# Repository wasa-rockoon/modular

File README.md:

# モジュラー電装

# バス

バスの物理規格は，2.54mmピッチのカードエッジコネクタとする．片面15ピンずつ．

CANを用いた通信プロトコルは [WCCP](https://github.com/wasa-rockoon/WCCP)を参照．

表
1. Vpp
2. Vcc 5V
3. Vdd 3.3V
4. VBAT 3V
5. GND
6. CAN Low
7. CAN High
8. GND
9. キー
10. JTMS, SWDIO
11. JTCK, SWCLK
12. JTDI
13. JTDO, TRACESWO
14. /JNTRST
15. /RESET
裏

16 ~ 23, 25 ~ 30. テスト用プローブ 1 ~ 8, 9 ~ 14

24. キー

## Vpp, Vcc, Vdd, GND

電源モジュールから供給される．バスからのVpp供給は小電流に限る．大電流が必要なモジュールには電源モジュールまたは外部から直接供給すること．

## CAN High, CAN Low

5V CANバス, Normal CAN 1Mbps

## SWCLK, SWDIO, RST

STM32書き込み・デバッグ用

# モジュール一覧

## ベース基板

6個のモジュールを搭載できるベース基板．
カードエッジコネクタのうち1つを書き込み・デバッグ用とする．

- カードエッジコネクタ x6
- CANバスコネクタ x2
- STLink 書き込み・デバッグ用コネクタ x1
- テスト用カードエッジ

### CANバスコネクタ

ベース基板に取り付けないモジュールとの中距離接続に用いる．

1. Vpp
2. CAN Low
3. CAN High
4. GND

Vcc, Vddはモジュール側で自給する．

接続しない場合は，CAN Low と CAN High との間に終端抵抗（120 Ω）を必ず接続すること．

## Battery Power

- 5Vおよび3.3Vの電源を供給
- 各系統の電圧および電流を測定

### 接続

- 電源供給（6V~18V）：XH (1: V+, 2: GND)

### インターフェース

- 主電源スイッチ
- バックアップ電源スイッチ

### 出力パケット

#### B （Battery）

| Type | Data | Description |
| --- | --- | --- |
| P | float16 | 供給電源電圧 [V] |
| C | float16 | 5V系電圧 [V] |
| D | float16 | 3.3V系電圧 [V] |
| c | float16 | 5V系電圧 [A] |
| d | float16 | 3.3V系電流 [A] |

## Battery Power V2

- 5Vおよび3.3Vの電源を供給
- 各系統の電圧および電流を測定
- 外部に5Vまたは3.3Vの電源を供給
- バッテリー温度を測定し，ヒーターを駆動

### 接続

- 電源供給1（6V~18V）：XH (1: V+, 2: GND)
- 電源供給2（6V~18V）：XH (1: V+, 2: GND)
- ヒーター：PH (1: Heater+, 2: GND, 3: temperature)
- 外部供給出力（5V or 3.3V）：PH (1: V+, 2: GND, 3: flight pin)
- 外部電源スイッチ：PH

### インターフェース

- 5V・3.3V系電源スイッチ（外部スイッチとどちらかがONならば供給）

### 出力パケット

#### B （Battery）

| Type | Data | Description |
| --- | --- | --- |
| P | float16 | 供給電源電圧 [V] |
| C | float16 | 5V系電圧 [V] |
| D | float16 | 3.3V系電圧 [V] |
| c | float16 | 5V系電圧 [A] |
| d | float16 | 3.3V系電流 [A] |

## Comm&Log

- LoRa（ES920LR）通信
- TWELITE 通信
- Micro SD カードにログを記録

### 接続

- LoRa アンテナ：U.FL
- TWELITE アンテナ：U.FL

### インターフェース

- Micro SD カードスロット

## LoRa

- LoRa（ES920LR）通信（2ch）

### 接続

- LoRa アンテナx2：U.FL

## Igniter Driver

- 発射条件を判定しイグナイタを駆動
- 供給電圧，電流，イグナイタ抵抗値を測定

### 接続

- イグナイタ用供給（6V~12V）：XH (1: V+, 2: GND)
- イグナイタ出力：XH (1: V+, 2: GND)

### インターフェース

- 警報ブザー

## Nav

- 9軸センサ（BMX055）
- 気圧センサ（BME280）
- GNSS

### 接続

- GPS パッシブアンテナ：U.FL
- UART （外部GPS用）：PH
- I2C （拡張用）：PH

## INS

- 9軸センサ（BNO055）
- 気圧センサ（BME280）
- GNSS (NEO-M9N-00B)

### 接続

- GPS アクティブアンテナ：U.FL
- サーミスタ：PH
- UART （拡張用）：PH
- I2C （拡張用）：PH

## RCS

- 電磁バルブ制御x4
- バルブ用電源（24V）供給
- 圧力計測（1MPaG）x2
- 推力計測x2
- 温度計測

### 接続

- バルブAB：PH (1: A+, 2: A-, 3: B+, 4: B-)
- バルブCD：PH (1: C+, 2: C-, 3: D+, 4: D-)
- ロードセルX：ZH (1: Vdd, 2: GND, 3: Signal+, 4: Signal-)
- ロードセルY：ZH (1: Vdd, 2: GND, 3: Signal+, 4: Signal-)
- 圧力センサ1：ZH (1: Vcc, 2: GND, 3: Signal)
- 圧力センサ2：ZH (1: Vcc, 2: GND, 3: Signal)
- サーミスタ：ZH

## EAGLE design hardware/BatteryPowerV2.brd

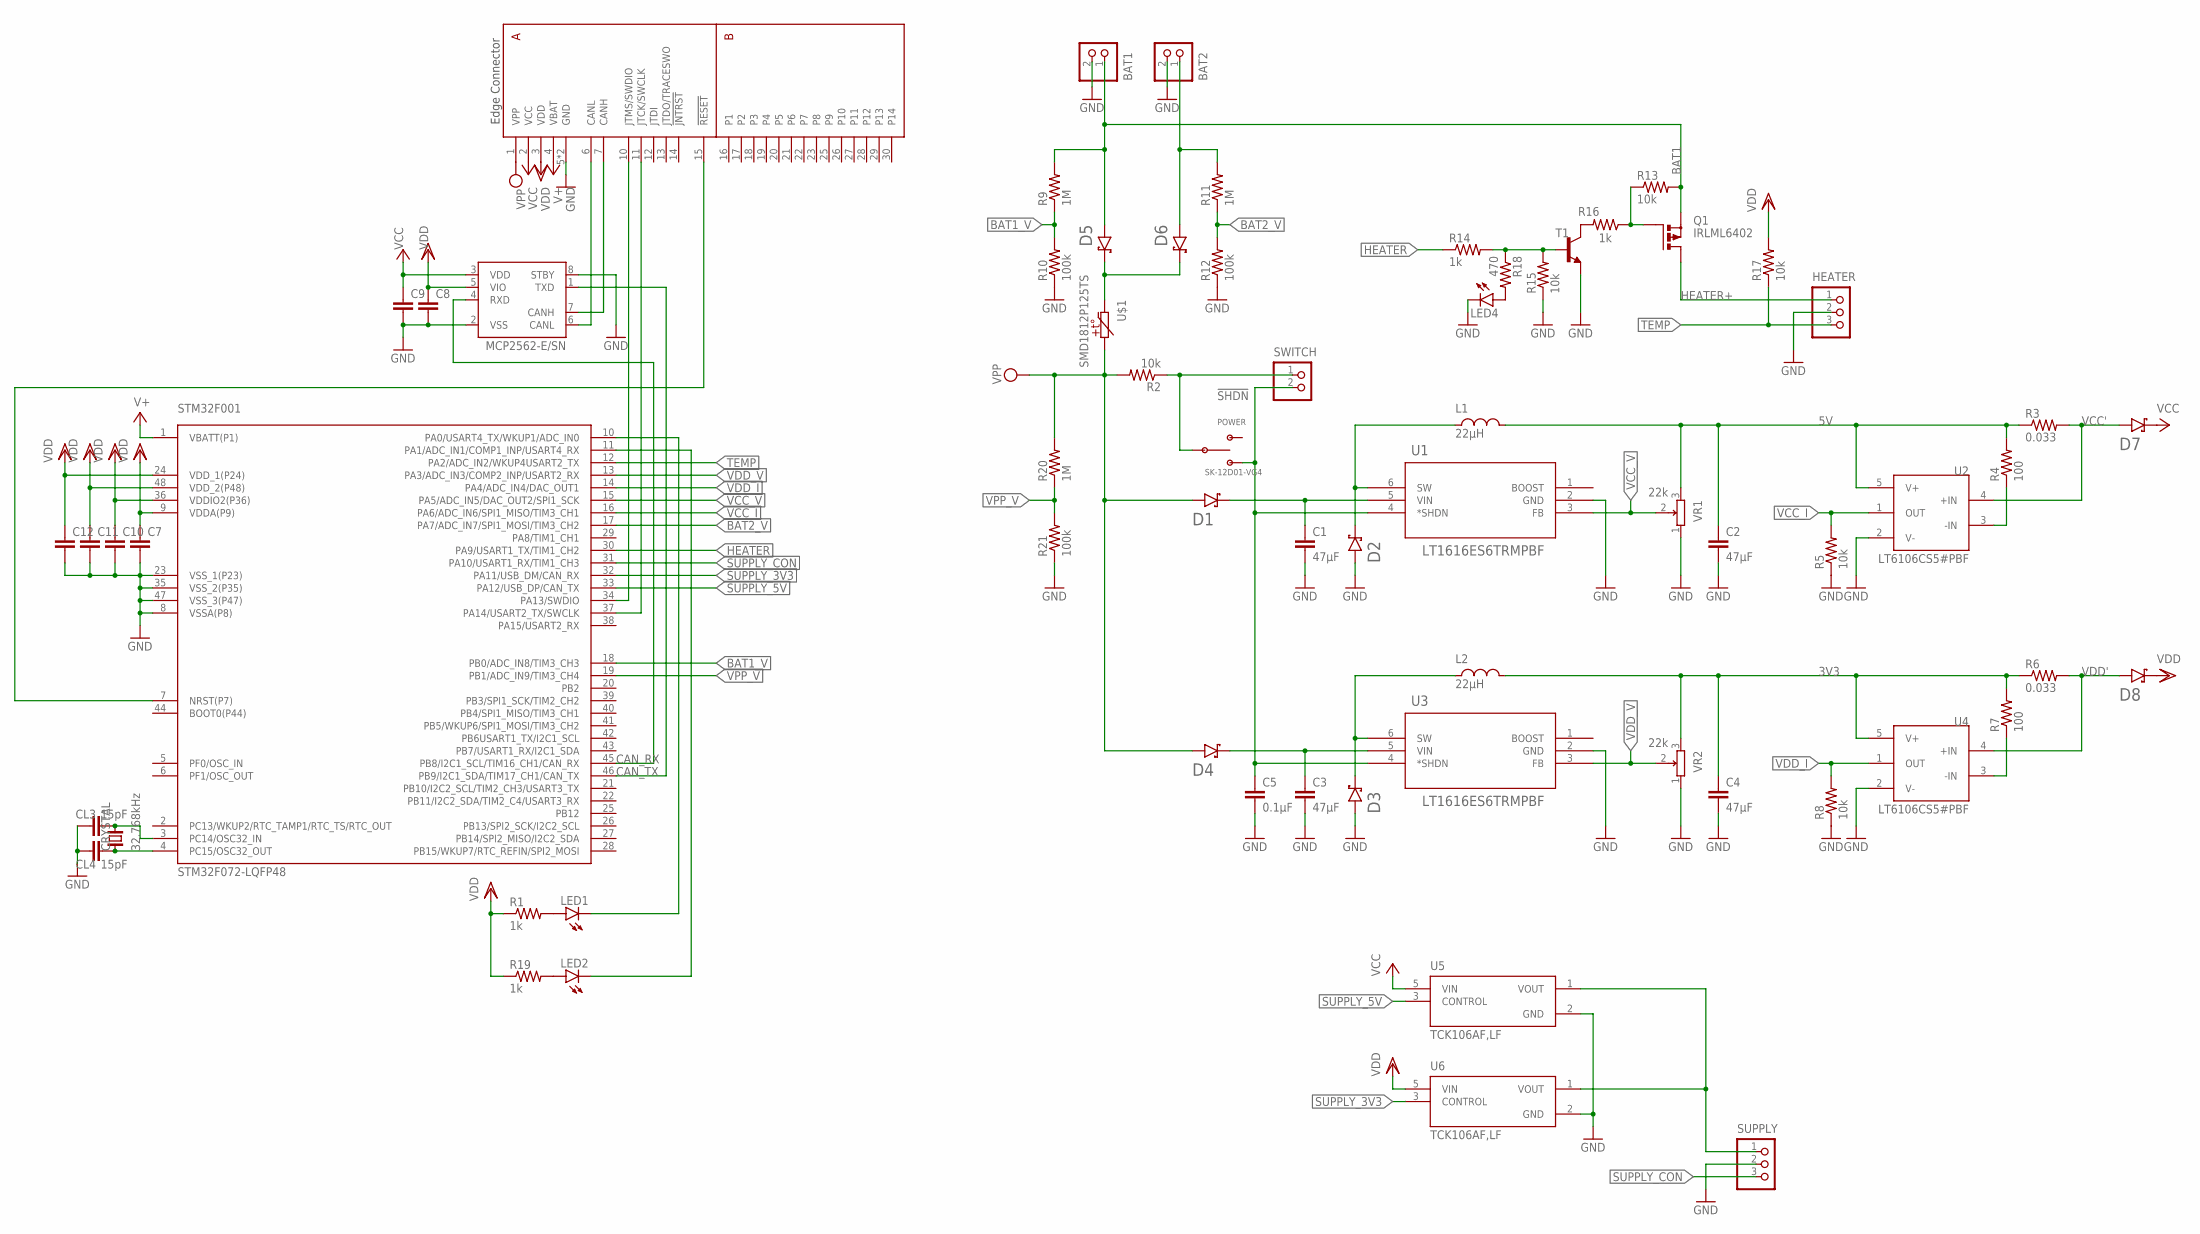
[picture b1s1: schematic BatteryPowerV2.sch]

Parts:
BAT1, BAT2: S2B-XH-A
C1, C2, C3, C4: 47µF; C0603
C5: 0.1µF; C0603
C7, C8, C9, C10, C11, C12: C-EUC0603K; C0603K
CL3, CL4: 15pF; C0603K
CRYSTAL: 32.768kHz; FC-255
D1, D2, D3, D4, D5, D6, D7, D8: CUHS20S30
HEATER: S3B-PH-K-S
L1, L2: 22µH; NR10050
LED1, LED2: LEDCHIP-LED0603; CHIP-LED0603
LED4: LEDCHIPLED_0603; CHIPLED_0603
MCP2562: MCP2562-E/SN; SOIC127P600X175-8N
POWER: SK-12D01-VG4
Q1: IRLML6402; SOT-23
R1, R14, R16, R19: 1k; R0603
R2, R5, R8, R13, R15, R17: 10k; R0603
R3, R6: 0.033; R0603
R4, R7: 100; R0603
R9, R11, R20: 1M; R0603
R10, R12, R21: 100k; R0603
R18: 470; R0603
STM32F001: STM32F072-LQFP48; LQFP48
SUPPLY: S3B-PH-K-S
SWITCH: S2B-PH-K-S
T1: -NPN-SOT23-EBC; SOT23-EBC
U1, U3: LT1616ES6TRMPBF; SOT-6_S
U2, U4: LT6106CS5#PBF; SOT95P280X100-5N_LT6106CS5#PBF
U5, U6: TCK106AF,LF; IC_TCK106AF,LF
U$1: SMD1812P125TS; SMD1812P
U$2: EDGE30
VR1, VR2: 22k; PVZ3A

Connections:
3V3: C4.1, L2.2, R6.1, R7.2, U4.5 (V+), VR2.3
5V: C2.1, L1.2, R3.1, R4.2, U2.5 (V+), VR1.3
!SHDN!: C5.1, POWER.B, SWITCH.2, U1.4 (*SHDN), U3.4 (*SHDN)
BAT1: BAT1.1, D5.A, Q1.P2 (S), R9.2, R13.2
BAT1_V: R9.1, R10.2, STM32F001.18 (PB0/ADC_IN8/TIM3_CH3)
BAT2: BAT2.1, D6.A, R11.2
BAT2_V: R11.1, R12.2, STM32F001.17 (PA7/ADC_IN7/SPI1_MOSI/TIM3_CH2)
CANH1: MCP2562.7 (CANH), U$2.7 (CANH)
CANL1: MCP2562.6 (CANL), U$2.6 (CANL)
CAN_RX: MCP2562.4 (RXD), STM32F001.45 (PB8/I2C1_SCL/TIM16_CH1/CAN_RX)
CAN_TX: MCP2562.1 (TXD), STM32F001.46 (PB9/I2C1_SDA/TIM17_CH1/CAN_TX)
GND: BAT1.2, BAT2.2, C1.2, C2.2, C3.2, C4.2, C5.2, C7.2, C8.2, C9.2, C10.2, C11.2, C12.2, CL3.1, CL4.1, D2.A, D3.A, HEATER.2, LED4.C, MCP2562.2 (VSS), MCP2562.8 (STBY), R5.1, R8.1, R10.1, R12.1, R15.1, R21.1, STM32F001.8 (VSSA(P8)), STM32F001.23 (VSS_1(P23)), STM32F001.35 (VSS_2(P35)), STM32F001.47 (VSS_3(P47)), SUPPLY.2, T1.E, U1.2 (GND), U2.2 (V-), U3.2 (GND), U4.2 (V-), U5.2 (GND), U6.2 (GND), U$2.5 (GND), U$2.8 (GND), VR1.1, VR2.1
HEATER: R14.1, STM32F001.30 (PA9/USART1_TX/TIM1_CH2)
HEATER+: HEATER.1, Q1.P3 (D)
unnamed: SUPPLY.1, U5.1 (VOUT), U6.1 (VOUT)
unnamed: R4.1, U2.3 (-IN)
unnamed: Q1.P1 (G), R13.1, R16.1
unnamed: LED2.C, STM32F001.11 (PA1/ADC_IN1/COMP1_INP/USART4_RX)
unnamed: R7.1, U4.3 (-IN)
unnamed: POWER.C, R2.1, SWITCH.1
unnamed: LED2.A, R19.2
unnamed: R14.2, R15.2, R18.1, T1.B
unnamed: R16.2, T1.C
unnamed: LED4.A, R18.2
unnamed: CL4.2, CRYSTAL.1, STM32F001.4 (PC15/OSC32_OUT)
unnamed: CL3.2, CRYSTAL.2, STM32F001.3 (PC14/OSC32_IN)
unnamed: LED1.C, STM32F001.10 (PA0/USART4_TX/WKUP1/ADC_IN0)
unnamed: LED1.A, R1.2
NRST1: STM32F001.7 (NRST(P7)), U$2.15 (!RESET!)
SUPPLY_3V3: STM32F001.32 (PA11/USB_DM/CAN_RX), U6.3 (CONTROL)
SUPPLY_5V: STM32F001.33 (PA12/USB_DP/CAN_TX), U5.3 (CONTROL)
SUPPLY_CON: STM32F001.31 (PA10/USART1_RX/TIM1_CH3), SUPPLY.3
SWCLK1: STM32F001.37 (PA14/USART2_TX/SWCLK), U$2.11 (JTCK/SWCLK)
SWDIO1: STM32F001.34 (PA13/SWDIO), U$2.10 (JTMS/SWDIO)
TEMP: HEATER.3, R17.1, STM32F001.12 (PA2/ADC_IN2/WKUP4USART2_TX)
VBAT: STM32F001.1 (VBATT(P1)), U$2.4 (VBAT)
VCC: C9.1, D7.C, MCP2562.3 (VDD), U5.5 (VIN), U$2.2 (VCC)
VCC': D7.A, R3.2, U2.4 (+IN)
VCC_I: R5.2, STM32F001.16 (PA6/ADC_IN6/SPI1_MISO/TIM3_CH1), U2.1 (OUT)
VCC_IN: C1.1, D1.C, U1.5 (VIN)
VCC_SW: D2.C, L1.1, U1.6 (SW)
VCC_V: STM32F001.15 (PA5/ADC_IN5/DAC_OUT2/SPI1_SCK), U1.3 (FB), VR1.2
VDD: C7.1, C8.1, C10.1, C11.1, C12.1, D8.C, MCP2562.5 (VIO), R1.1, R17.2, R19.1, STM32F001.9 (VDDA(P9)), STM32F001.24 (VDD_1(P24)), STM32F001.36 (VDDIO2(P36)), STM32F001.48 (VDD_2(P48)), U6.5 (VIN), U$2.3 (VDD)
VDD': D8.A, R6.2, U4.4 (+IN)
VDD_I: R8.2, STM32F001.14 (PA4/ADC_IN4/DAC_OUT1), U4.1 (OUT)
VDD_IN: C3.1, D4.C, U3.5 (VIN)
VDD_SW: D3.C, L2.1, U3.6 (SW)
VDD_V: STM32F001.13 (PA3/ADC_IN3/COMP2_INP/USART2_RX), U3.3 (FB), VR2.2
VPP: D1.A, D4.A, R2.2, R20.2, U$1.2, U$2.1 (VPP)
VPP_IN: D5.C, D6.C, U$1.1
VPP_V: R20.1, R21.2, STM32F001.19 (PB1/ADC_IN9/TIM3_CH4)

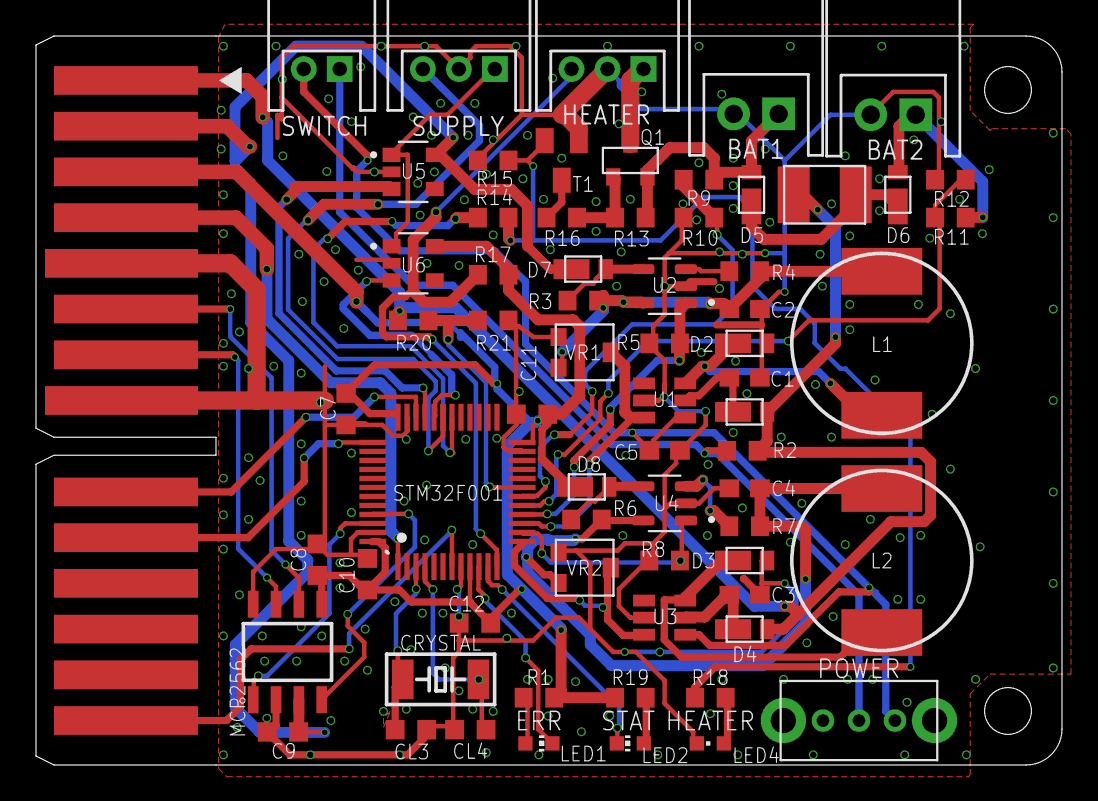
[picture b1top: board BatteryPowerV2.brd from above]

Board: 2 copper layers, 57.0 x 40.5 mm, 68 parts (0 on the bottom side), 51 nets.

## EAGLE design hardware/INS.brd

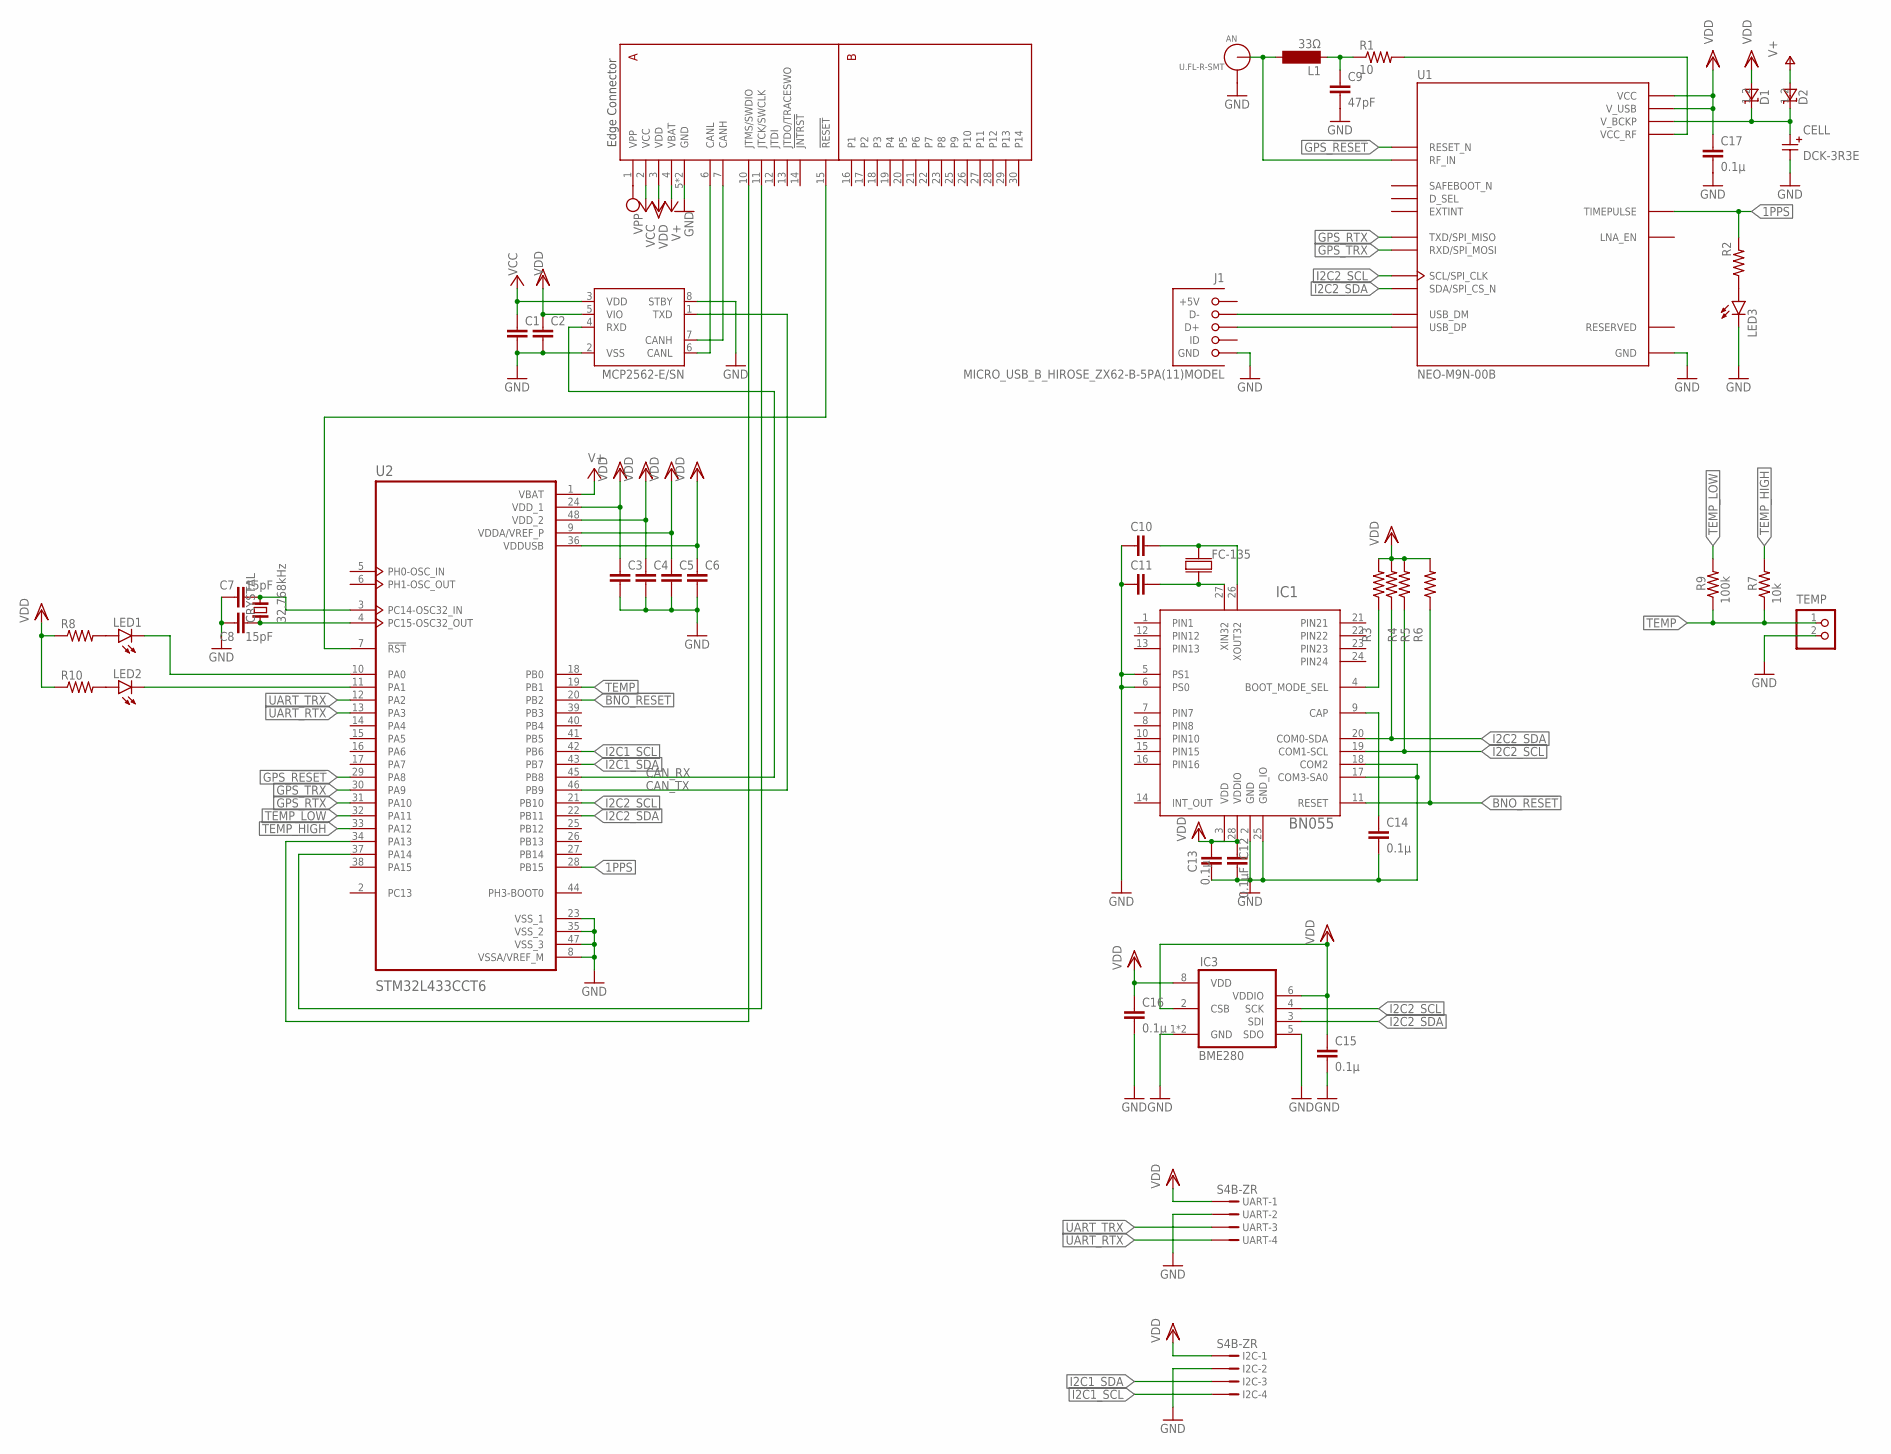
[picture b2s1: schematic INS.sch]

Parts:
AN: U.FL-R-SMT; U.FL_SMT
C1, C2, C3, C4, C5, C6: C-EUC0603K; C0603K
C7, C8: 15pF; C0603K
C9: 47pF; C0603
C10, C11: C-EUC0603; C0603
C12: 0.1µF; C0603
C13, C14, C15, C16, C17: 0.1µ; C0603
CELL: DCK-3R3E; DC,DCK
CRYSTAL: 32.768kHz; FC-255
D1, D2: RB521S-30TE61; SODFL1608X70N
FC-135: FC-135
I2C: S4B-ZR
IC1: BN055; LGA-28_3.80X5.20/0.5
IC3: BME280
J1: MICRO_USB_B_HIROSE_ZX62-B-5PA(11)MODEL; GHI-CONNECTORS_10118192-0001LF(MICRO-USB-B-AMPHENOL-FCI)
L1: 33Ω; SM-NE29
LED1, LED2, LED3: LEDCHIP-LED0603; CHIP-LED0603
MCP2562: MCP2562-E/SN; SOIC127P600X175-8N
R1: 10; R0603
R2, R3, R4, R5, R6, R8, R10: R-US_R0603; R0603
R7: 10k; R0603
R9: 100k; R0603
TEMP: S2B-PH-K-S
U1: NEO-M9N-00B; XCVR_NEO-M9N-00B
U2: STM32L433CCT6; QFP50P900X900X160-48N
U$2: EDGE30
UART: S4B-ZR

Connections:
1PPS: LED3.A, R2.1, R2.2, U1.3 (TIMEPULSE), U2.28 (PB15)
ANT: AN.SIG (ANT), L1.2, U1.11 (RF_IN)
BNO_!RESET!: IC1.11 (RESET), R6.1, U2.20 (PB2)
CANH1: MCP2562.7 (CANH), U$2.7 (CANH)
CANL1: MCP2562.6 (CANL), U$2.6 (CANL)
CAN_RX: MCP2562.4 (RXD), U2.45 (PB8)
CAN_TX: MCP2562.1 (TXD), U2.46 (PB9)
GND: AN.GND1, AN.GND2, C1.2, C2.2, C3.2, C4.2, C5.2, C6.2, C7.1, C8.1, C9.2, C10.1, C11.1, C12.2, C13.2, C14.2, C15.2, C16.2, C17.2, CELL.-, I2C.2, IC1.2 (GND), IC1.5 (PS1), IC1.6 (PS0), IC1.17 (COM3-SA0), IC1.18 (COM2), IC1.25 (GND_IO), IC3.1 (GND), IC3.5 (SDO), IC3.7 (GND), J1.CGND1 (GND), J1.CGND2 (GND), J1.CGND3 (GND), J1.CGND4 (GND), J1.CGND5 (GND), J1.CGND6 (GND), J1.GND, LED3.C, MCP2562.2 (VSS), MCP2562.8 (STBY), TEMP.2, U1.10 (GND), U1.12 (GND), U1.13 (GND), U1.24 (GND), U2.8 (VSSA/VREF_M), U2.23 (VSS_1), U2.35 (VSS_2), U2.47 (VSS_3), U$2.5 (GND), U$2.8 (GND), UART.2
GPS_!RESET!: U1.8 (RESET_N), U2.29 (PA8)
GPS_RTX: U1.20 (TXD/SPI_MISO), U2.31 (PA10)
GPS_TRX: U1.21 (RXD/SPI_MOSI), U2.30 (PA9)
I2C1_SCL: I2C.4, U2.42 (PB6)
I2C1_SDA: I2C.3, U2.43 (PB7)
I2C2_SCL: IC1.19 (COM1-SCL), IC3.4 (SCK), R5.1, U1.19 (SCL/SPI_CLK), U2.21 (PB10)
I2C2_SDA: IC1.20 (COM0-SDA), IC3.3 (SDI), R4.1, U1.18 (SDA/SPI_CS_N), U2.22 (PB11)
unnamed: R1.2, U1.9 (VCC_RF)
unnamed: U2.7 (!RST), U$2.15 (!RESET!)
unnamed: IC1.4 (BOOT_MODE_SEL), R3.1
unnamed: LED1.C, U2.10 (PA0)
unnamed: C9.1, L1.1, R1.1
unnamed: LED2.C, U2.11 (PA1)
unnamed: C14.1, IC1.9 (CAP)
unnamed: CELL.+, D1.1 (K), D2.1 (K), U1.22 (V_BCKP)
unnamed: LED2.A, R10.2
unnamed: C11.2, FC-135.P$2, IC1.27 (XIN32)
unnamed: C10.2, FC-135.P$1, IC1.26 (XOUT32)
unnamed: C8.2, CRYSTAL.1, U2.4 (PC15-OSC32_OUT)
unnamed: C7.2, CRYSTAL.2, U2.3 (PC14-OSC32_IN)
unnamed: LED1.A, R8.2
SWCLK1: U2.37 (PA14), U$2.11 (JTCK/SWCLK)
SWDIO1: U2.34 (PA13), U$2.10 (JTMS/SWDIO)
TEMP: R7.1, R9.1, TEMP.1, U2.19 (PB1)
TEMP_HIGH: R7.2, U2.33 (PA12)
TEMP_LOW: R9.2, U2.32 (PA11)
UART_RTX: U2.13 (PA3), UART.4
UART_TRX: U2.12 (PA2), UART.3
USB_D+: J1.D+, U1.6 (USB_DP)
USB_D-: J1.D-, U1.5 (USB_DM)
VBAT: D2.2 (A), U2.1 (VBAT), U$2.4 (VBAT)
VCC: C1.1, MCP2562.3 (VDD), U$2.2 (VCC)
VDD: C2.1, C3.1, C4.1, C5.1, C6.1, C12.1, C13.1, C15.1, C16.1, C17.1, D1.2 (A), I2C.1, IC1.3 (VDD), IC1.28 (VDDIO), IC3.2 (CSB), IC3.6 (VDDIO), IC3.8 (VDD), MCP2562.5 (VIO), R3.2, R4.2, R5.2, R6.2, R8.1, R10.1, U1.7 (V_USB), U1.23 (VCC), U2.9 (VDDA/VREF_P), U2.24 (VDD_1), U2.36 (VDDUSB), U2.48 (VDD_2), U$2.3 (VDD), UART.1
VPP: U$2.1 (VPP)

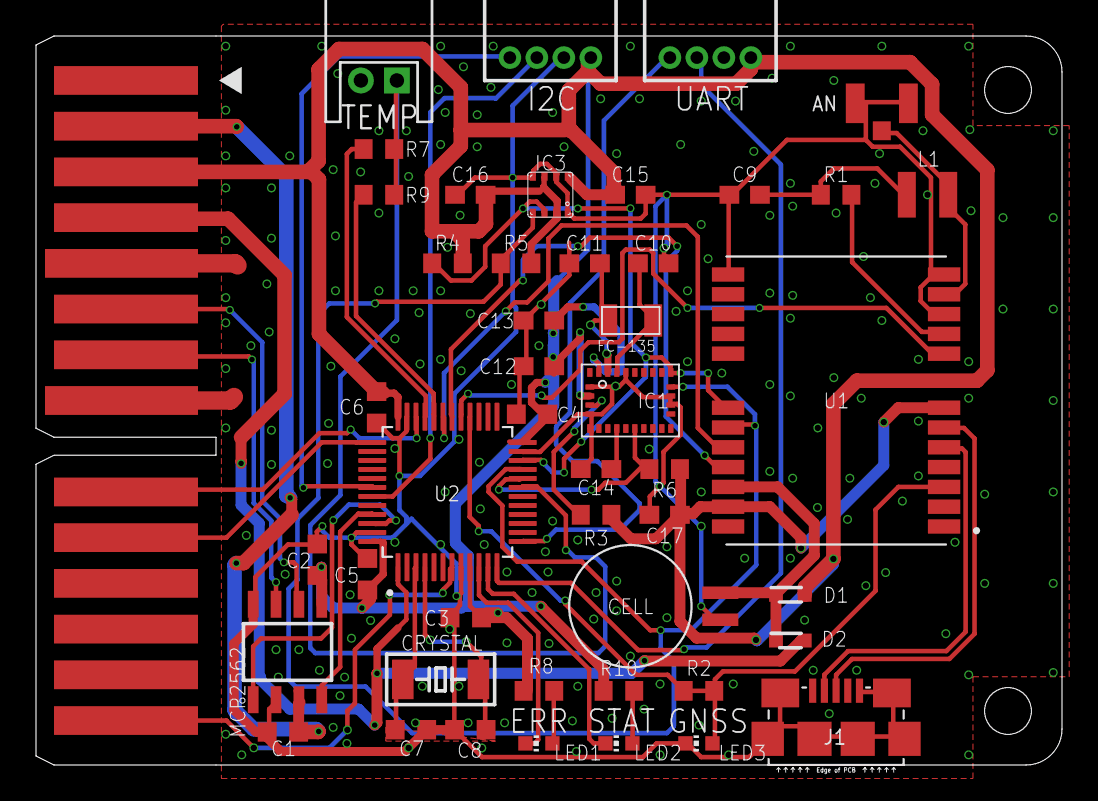
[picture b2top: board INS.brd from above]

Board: 2 copper layers, 57.0 x 40.5 mm, 47 parts (0 on the bottom side), 41 nets.

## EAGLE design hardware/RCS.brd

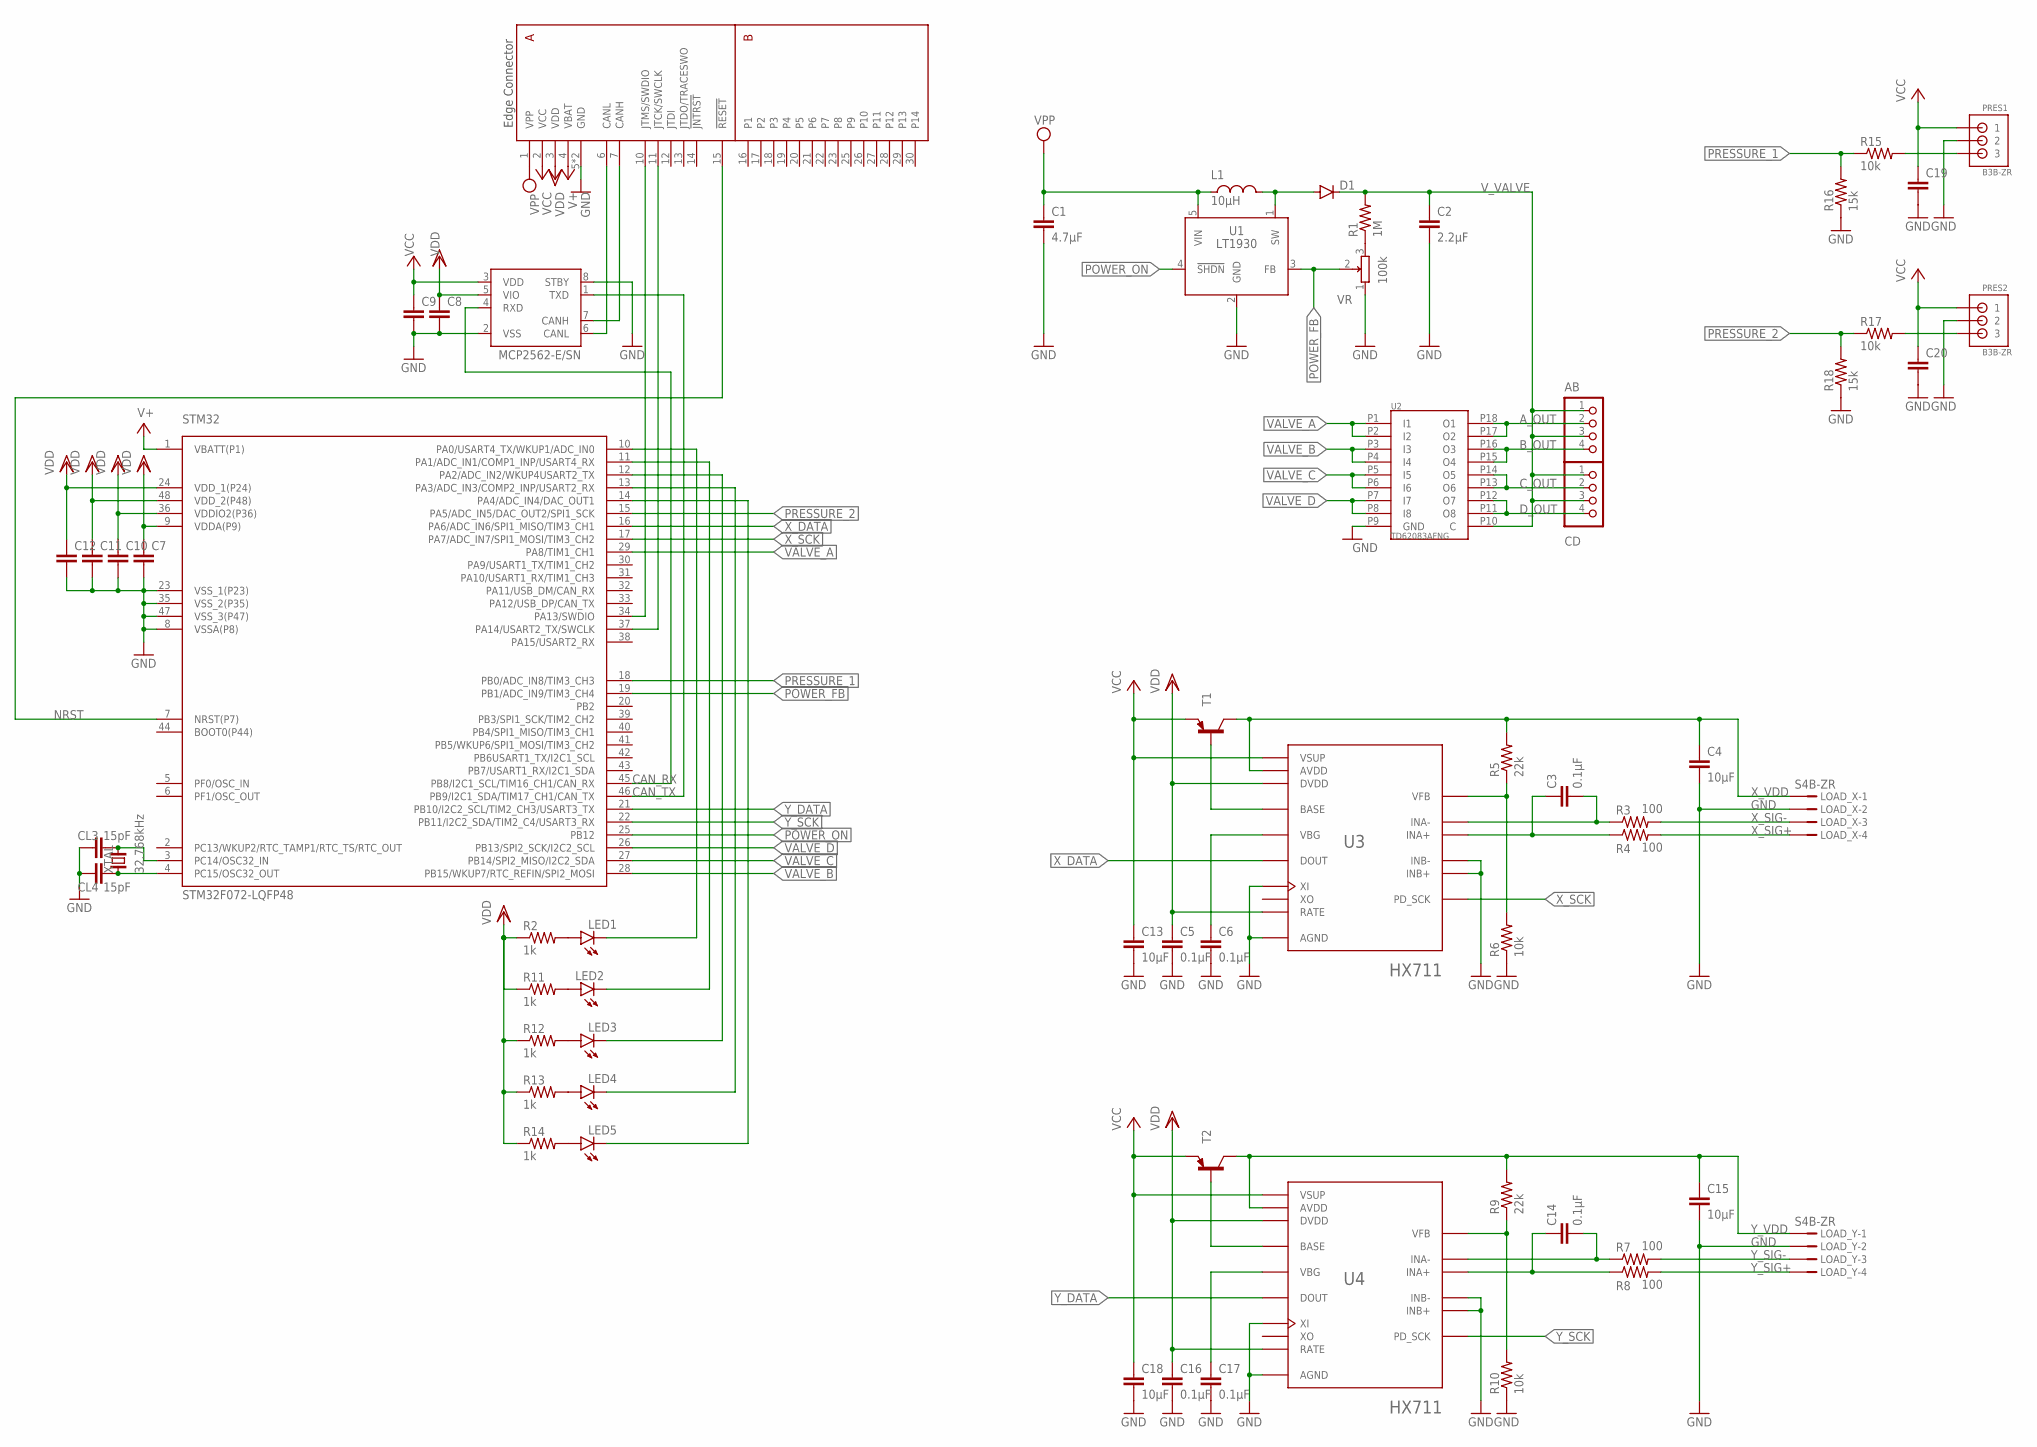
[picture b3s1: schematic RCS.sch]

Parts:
AB: S4B-PH-K-S
C1: 4.7µF; C0603
C2: 2.2µF; C0603
C3, C5, C6, C14, C16, C17: 0.1µF; C0603
C4, C13, C15, C18: 10µF; C0603
C7, C8, C9, C10, C11, C12: C-EUC0603K; C0603K
C19, C20: C-EUC0603; C0603
CD: S4B-PH-K-S
CL3, CL4: 15pF; C0603K
D1: DIODE-SOD123; SOD123
L1: 10µH; NR10050
LED1, LED2, LED3, LED4, LED5: LEDCHIP-LED0603; CHIP-LED0603
LOAD_X: S4B-ZR
LOAD_Y: S4B-ZR
MCP1: MCP2562-E/SN; SOIC127P600X175-8N
PRES1, PRES2: B3B-ZR
R1: 1M; R0603
R2, R11, R12, R13, R14: 1k; R0603
R3, R4, R7, R8: 100; R0603
R5, R9: 22k; R0603
R6, R10, R15, R17: 10k; R0603
R16, R18: 15k; R0603
STM32: STM32F072-LQFP48; LQFP48
T1, T2: BC857A-PNP-SOT23-BEC; SOT23-BEC
U1: LT1930; SOT95P240X110-5N
U2: TD62083AFNG; SSOP18-P-225-0.65
U3, U4: HX711; SOP127P600X180-16N
U$2: EDGE30
VR: 100k; PVZ3A
XTAL: 32.768kHz; FC-255

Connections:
A_OUT: AB.2, U2.P17 (O2), U2.P18 (O1)
B_OUT: AB.4, U2.P15 (O4), U2.P16 (O3)
CANH1: MCP1.7 (CANH), U$2.7 (CANH)
CANL1: MCP1.6 (CANL), U$2.6 (CANL)
CAN_RX: MCP1.4 (RXD), STM32.45 (PB8/I2C1_SCL/TIM16_CH1/CAN_RX)
CAN_TX: MCP1.1 (TXD), STM32.46 (PB9/I2C1_SDA/TIM17_CH1/CAN_TX)
C_OUT: CD.2, U2.P13 (O6), U2.P14 (O5)
D_OUT: CD.4, U2.P11 (O8), U2.P12 (O7)
GND: C1.2, C2.2, C4.2, C5.2, C6.2, C7.2, C8.2, C9.2, C10.2, C11.2, C12.2, C13.2, C15.2, C16.2, C17.2, C18.2, C19.2, C20.2, CL3.1, CL4.1, LOAD_X.2, LOAD_Y.2, MCP1.2 (VSS), MCP1.8 (STBY), PRES1.2, PRES2.2, R6.1, R10.1, R16.1, R18.1, STM32.8 (VSSA(P8)), STM32.23 (VSS_1(P23)), STM32.35 (VSS_2(P35)), STM32.47 (VSS_3(P47)), U1.2 (GND), U2.P9 (GND), U3.5 (AGND), U3.9 (INB-), U3.10 (INB+), U3.14 (XI), U4.5 (AGND), U4.9 (INB-), U4.10 (INB+), U4.14 (XI), U$2.5 (GND), U$2.8 (GND), VR.1
unnamed: R1.1, VR.3
unnamed: D1.A, L1.2, U1.1 (SW)
unnamed: C3.2, R3.1, U3.7 (INA-)
unnamed: C3.1, R4.1, U3.8 (INA+)
unnamed: R5.1, R6.2, U3.4 (VFB)
unnamed: T1.B, U3.2 (BASE)
unnamed: C6.1, U3.6 (VBG)
unnamed: PRES2.3, R17.2
unnamed: C14.2, R7.1, U4.7 (INA-)
unnamed: C14.1, R8.1, U4.8 (INA+)
unnamed: T2.B, U4.2 (BASE)
unnamed: C17.1, U4.6 (VBG)
unnamed: R9.1, R10.2, U4.4 (VFB)
unnamed: PRES1.3, R15.2
unnamed: LED3.C, STM32.12 (PA2/ADC_IN2/WKUP4USART2_TX)
unnamed: LED3.A, R12.2
unnamed: LED4.C, STM32.13 (PA3/ADC_IN3/COMP2_INP/USART2_RX)
unnamed: LED4.A, R13.2
unnamed: LED5.C, STM32.14 (PA4/ADC_IN4/DAC_OUT1)
unnamed: LED5.A, R14.2
unnamed: CL3.2, STM32.3 (PC14/OSC32_IN), XTAL.2
unnamed: LED2.C, STM32.11 (PA1/ADC_IN1/COMP1_INP/USART4_RX)
unnamed: LED2.A, R11.2
unnamed: LED1.C, STM32.10 (PA0/USART4_TX/WKUP1/ADC_IN0)
unnamed: CL4.2, STM32.4 (PC15/OSC32_OUT), XTAL.1
unnamed: LED1.A, R2.2
NRST: STM32.7 (NRST(P7)), U$2.15 (!RESET!)
POWER_FB: STM32.19 (PB1/ADC_IN9/TIM3_CH4), U1.3 (FB), VR.2
POWER_ON: STM32.25 (PB12), U1.4 (!SHDN!)
PRESSURE_1: R15.1, R16.2, STM32.18 (PB0/ADC_IN8/TIM3_CH3)
PRESSURE_2: R17.1, R18.2, STM32.15 (PA5/ADC_IN5/DAC_OUT2/SPI1_SCK)
SWCLK1: STM32.37 (PA14/USART2_TX/SWCLK), U$2.11 (JTCK/SWCLK)
SWDIO1: STM32.34 (PA13/SWDIO), U$2.10 (JTMS/SWDIO)
V+: STM32.1 (VBATT(P1))
VALVE_A: STM32.29 (PA8/TIM1_CH1), U2.P1 (I1), U2.P2 (I2)
VALVE_B: STM32.28 (PB15/WKUP7/RTC_REFIN/SPI2_MOSI), U2.P3 (I3), U2.P4 (I4)
VALVE_C: STM32.27 (PB14/SPI2_MISO/I2C2_SDA), U2.P5 (I5), U2.P6 (I6)
VALVE_D: STM32.26 (PB13/SPI2_SCK/I2C2_SCL), U2.P7 (I7), U2.P8 (I8)
VBAT: U$2.4 (VBAT)
VCC: C9.1, C13.1, C18.1, C19.1, C20.1, MCP1.3 (VDD), PRES1.1, PRES2.1, T1.E, T2.E, U3.1 (VSUP), U4.1 (VSUP), U$2.2 (VCC)
VDD: C5.1, C7.1, C8.1, C10.1, C11.1, C12.1, C16.1, MCP1.5 (VIO), R2.1, R11.1, R12.1, R13.1, R14.1, STM32.9 (VDDA(P9)), STM32.24 (VDD_1(P24)), STM32.36 (VDDIO2(P36)), STM32.48 (VDD_2(P48)), U3.15 (RATE), U3.16 (DVDD), U4.15 (RATE), U4.16 (DVDD), U$2.3 (VDD)
VPP: C1.1, L1.1, U1.5 (VIN), U$2.1 (VPP)
V_VALVE: AB.1, AB.3, C2.1, CD.1, CD.3, D1.C, R1.2, U2.P10 (C)
X_DATA: STM32.16 (PA6/ADC_IN6/SPI1_MISO/TIM3_CH1), U3.12 (DOUT)
X_SCK: STM32.17 (PA7/ADC_IN7/SPI1_MOSI/TIM3_CH2), U3.11 (PD_SCK)
X_SIG+: LOAD_X.4, R4.2
X_SIG-: LOAD_X.3, R3.2
X_VDD: C4.1, LOAD_X.1, R5.2, T1.C, U3.3 (AVDD)
Y_DATA: STM32.21 (PB10/I2C2_SCL/TIM2_CH3/USART3_TX), U4.12 (DOUT)
Y_SCK: STM32.22 (PB11/I2C2_SDA/TIM2_C4/USART3_RX), U4.11 (PD_SCK)
Y_SIG+: LOAD_Y.4, R8.2
Y_SIG-: LOAD_Y.3, R7.2
Y_VDD: C15.1, LOAD_Y.1, R9.2, T2.C, U4.3 (AVDD)

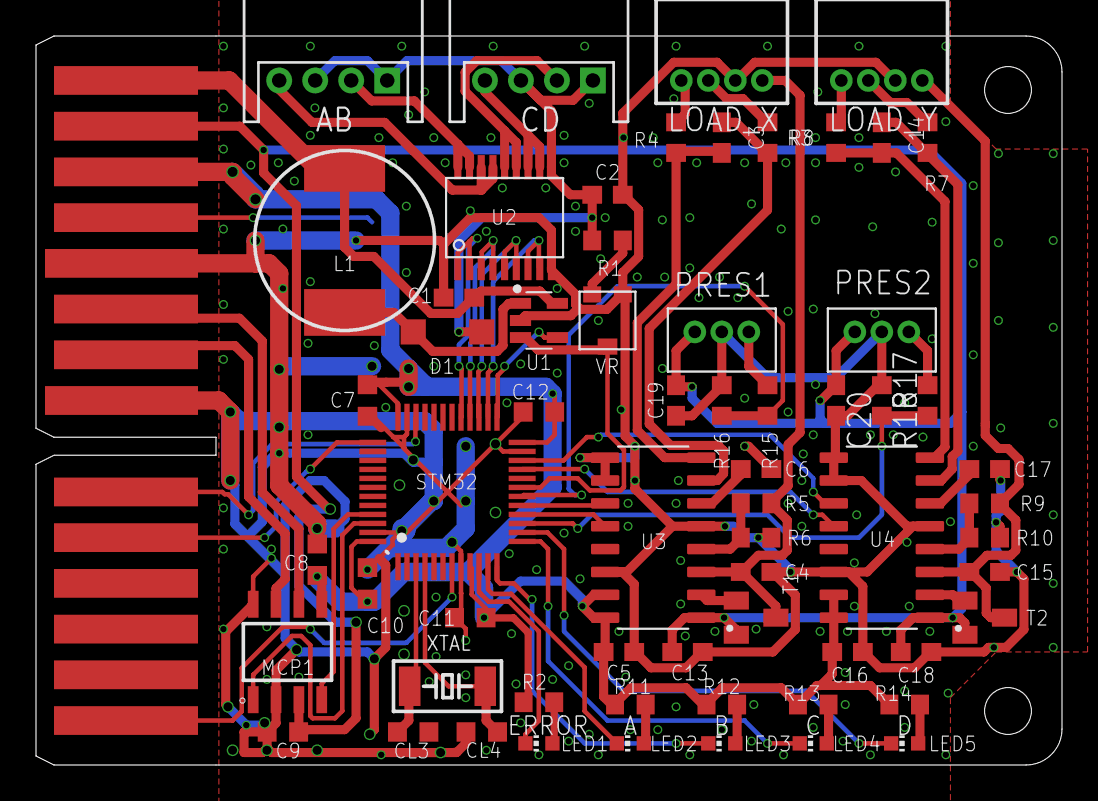
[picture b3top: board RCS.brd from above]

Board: 2 copper layers, 57.0 x 40.5 mm, 64 parts (0 on the bottom side), 60 nets.

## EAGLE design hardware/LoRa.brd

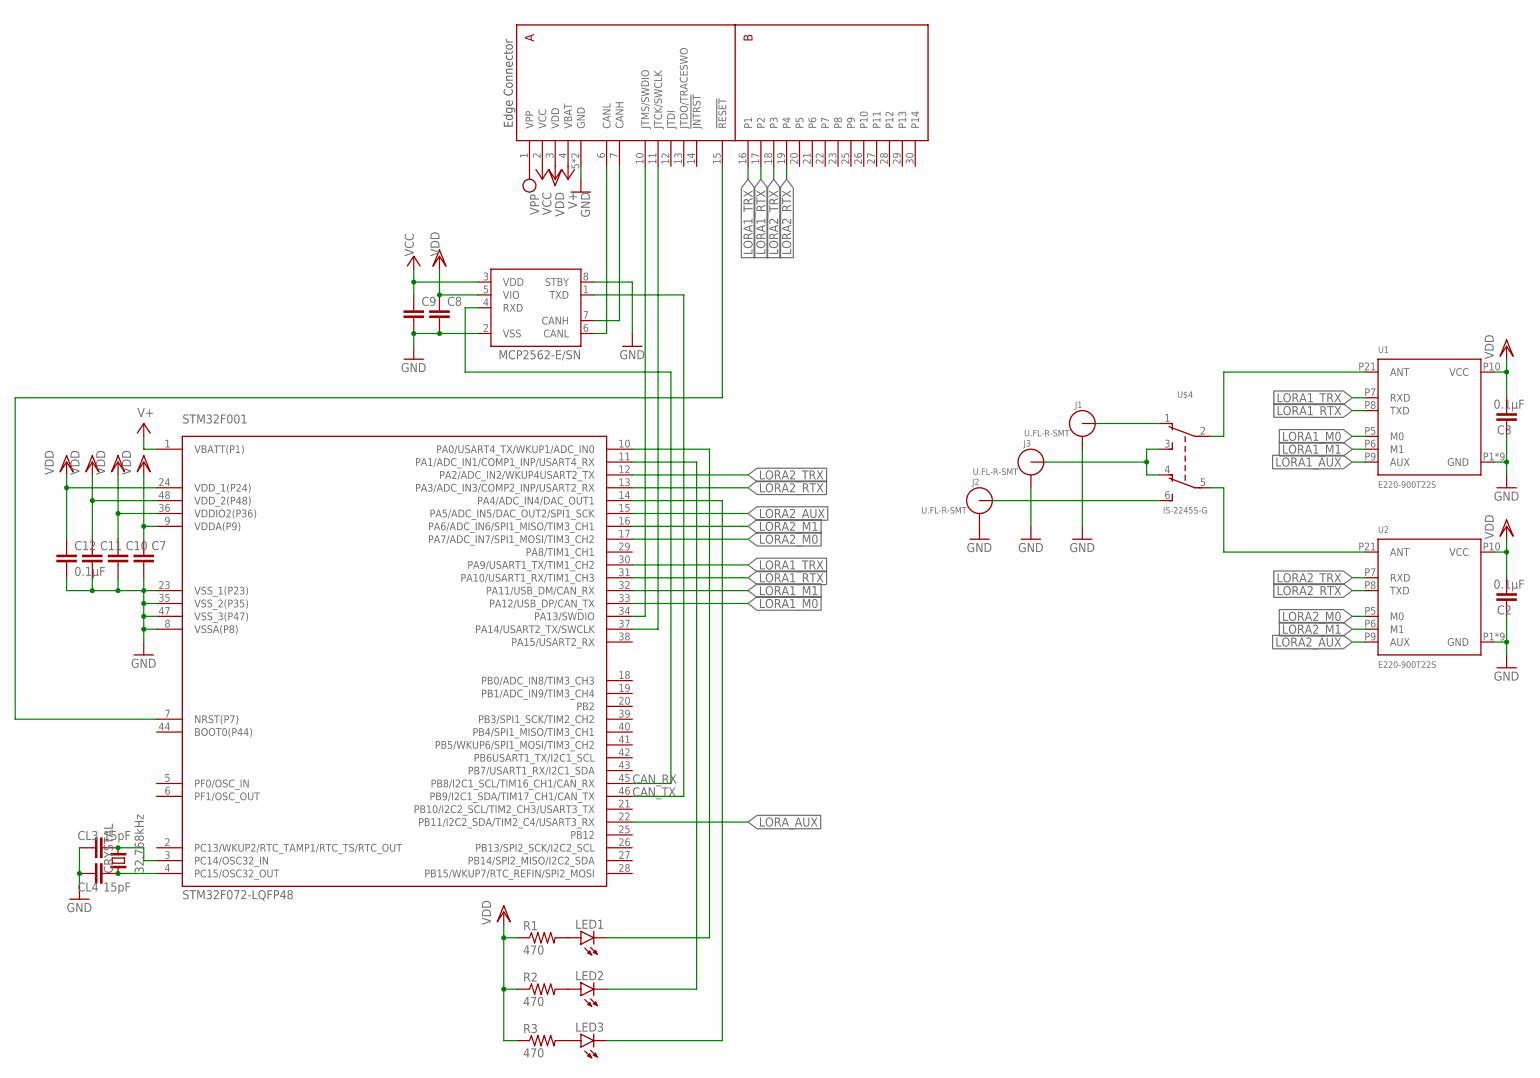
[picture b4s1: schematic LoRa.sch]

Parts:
C2, C3, C12: 0.1µF; C0603K
C7, C8, C9, C10, C11: C-EUC0603K; C0603K
CL3, CL4: 15pF; C0603K
CRYSTAL: 32.768kHz; FC-255
J1, J2, J3: U.FL-R-SMT; U.FL_SMT
LED1, LED2, LED3: LEDCHIP-LED0603; CHIP-LED0603
MCP1: MCP2562-E/SN; SOIC127P600X175-8N
R1, R2, R3: 470; R0603
STM32F001: STM32F072-LQFP48; LQFP48
U1, U2: E220-900T22S
U$2: EDGE30
U$4: IS-2245S-G

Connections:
CANH1: MCP1.7 (CANH), U$2.7 (CANH)
CANL1: MCP1.6 (CANL), U$2.6 (CANL)
CAN_RX: MCP1.4 (RXD), STM32F001.45 (PB8/I2C1_SCL/TIM16_CH1/CAN_RX)
CAN_TX: MCP1.1 (TXD), STM32F001.46 (PB9/I2C1_SDA/TIM17_CH1/CAN_TX)
GND: C2.1, C3.1, C7.2, C8.2, C9.2, C10.2, C11.2, C12.2, CL3.1, CL4.1, J1.GND1, J1.GND2, J2.GND1, J2.GND2, J3.GND1, J3.GND2, MCP1.2 (VSS), MCP1.8 (STBY), STM32F001.8 (VSSA(P8)), STM32F001.23 (VSS_1(P23)), STM32F001.35 (VSS_2(P35)), STM32F001.47 (VSS_3(P47)), U1.P1 (GND), U1.P2 (GND), U1.P3 (GND), U1.P4 (GND), U1.P11 (GND), U1.P13 (GND), U1.P19 (GND), U1.P20 (GND), U1.P22 (GND), U2.P1 (GND), U2.P2 (GND), U2.P3 (GND), U2.P4 (GND), U2.P11 (GND), U2.P13 (GND), U2.P19 (GND), U2.P20 (GND), U2.P22 (GND), U$2.5 (GND), U$2.8 (GND)
LORA1_M0: STM32F001.33 (PA12/USB_DP/CAN_TX), U1.P5 (M0)
LORA1_M1: STM32F001.32 (PA11/USB_DM/CAN_RX), U1.P6 (M1)
LORA1_RTX: STM32F001.31 (PA10/USART1_RX/TIM1_CH3), U1.P8 (TXD), U$2.17 (P2)
LORA1_TRX: STM32F001.30 (PA9/USART1_TX/TIM1_CH2), U1.P7 (RXD), U$2.16 (P1)
LORA2_AUX: STM32F001.15 (PA5/ADC_IN5/DAC_OUT2/SPI1_SCK), U2.P9 (AUX)
LORA2_M0: STM32F001.17 (PA7/ADC_IN7/SPI1_MOSI/TIM3_CH2), U2.P5 (M0)
LORA2_M1: STM32F001.16 (PA6/ADC_IN6/SPI1_MISO/TIM3_CH1), U2.P6 (M1)
LORA2_RTX: STM32F001.13 (PA3/ADC_IN3/COMP2_INP/USART2_RX), U2.P8 (TXD), U$2.19 (P4)
LORA2_TRX: STM32F001.12 (PA2/ADC_IN2/WKUP4USART2_TX), U2.P7 (RXD), U$2.18 (P3)
unnamed: U1.P21 (ANT), U$4.2
unnamed: U2.P21 (ANT), U$4.5
unnamed: LED2.A, R2.2
unnamed: J1.SIG (ANT), U$4.1
unnamed: LED3.C, STM32F001.14 (PA4/ADC_IN4/DAC_OUT1)
unnamed: J2.SIG (ANT), U$4.6
unnamed: J3.SIG (ANT), U$4.3, U$4.4
unnamed: LED3.A, R3.2
unnamed: LED1.C, STM32F001.10 (PA0/USART4_TX/WKUP1/ADC_IN0)
unnamed: CL4.2, CRYSTAL.1, STM32F001.4 (PC15/OSC32_OUT)
unnamed: CL3.2, CRYSTAL.2, STM32F001.3 (PC14/OSC32_IN)
unnamed: LED2.C, STM32F001.11 (PA1/ADC_IN1/COMP1_INP/USART4_RX)
unnamed: LED1.A, R1.2
NRST1: STM32F001.7 (NRST(P7)), U$2.15 (!RESET!)
SWCLK1: STM32F001.37 (PA14/USART2_TX/SWCLK), U$2.11 (JTCK/SWCLK)
SWDIO1: STM32F001.34 (PA13/SWDIO), U$2.10 (JTMS/SWDIO)
VBAT: STM32F001.1 (VBATT(P1)), U$2.4 (VBAT)
VCC: C9.1, MCP1.3 (VDD), U$2.2 (VCC)
VDD: C2.2, C3.2, C7.1, C8.1, C10.1, C11.1, C12.1, MCP1.5 (VIO), R1.1, R2.1, R3.1, STM32F001.9 (VDDA(P9)), STM32F001.24 (VDD_1(P24)), STM32F001.36 (VDDIO2(P36)), STM32F001.48 (VDD_2(P48)), U1.P10 (VCC), U2.P10 (VCC), U$2.3 (VDD)
VPP: U$2.1 (VPP)

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

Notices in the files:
parts and their libraries:
FaBo-Switch: Released under the Creative Commons Attribution-ShareAlike 4.0 License
https://creativecommons.org/licenses/by-sa/4.0
